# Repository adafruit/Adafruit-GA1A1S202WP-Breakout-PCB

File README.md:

## Adafruit GA1A1S202WP Breakout PCB

<a href="http://www.adafruit.com/products/1384"><br/>
Click here to purchase one from the Adafruit shop</a>

PCB files for the Adafruit GA1A1S202WP Light Sensor. Format is EagleCAD schematic and board layout
* https://www.adafruit.com/products/1384

### DESCRIPTION
Upgrade a project that uses a photocell with the GA1A12S202 analog light sensor. Like a CdS photo-cell, the sensor does not require a microcontroller, the analog voltage output increases with the amount of light shining on the sensor face. This sensor has a lot of improvements that make it better for nearly any project.

The biggest improvement over plain photocells is a true log-lin relationship with light levels. Most light sensors have a linear relationship with light levels, which means that they're not very sensitive to changes in darkened areas and 'max' out very easily when there's a lot of light. Sometimes you can tweak a resistor to make them better in dark or bright light but its hard to get good performance at both ends. This sensor is logarithmic over a large dynamic range of 3 to 55,000 Lux, so it has a lot of sensitivity at low light levels but is also nearly impossible to "max out" so you can use it indoors or outdoors without changing code or calibration. Since the sensor is fabricated on a chip, there are also fewer manufacturing variations, so you won't have to calibrate the sensor from one board to another.

Using the sensor is easy as pie: connect the Vin to 2.3-6VDC, Gnd to ground and measure the analog output on OUT. It will range up to 3V (at extremely bright outdoor sunlight). On an Arduino, just use analogRead() with the OUT pin connected to an analog pin. For more information including graphs, power consumption, etc check out the datasheet in the Tech Details tab. On this breakout we placed a 68KΩ resistor from OUT to ground to turn the current into a voltage.

### License

Adafruit invests time and resources providing this open source design, please support Adafruit and open-source hardware by purchasing products from [Adafruit.com](https://www.adafruit.com)!

Designed by Adafruit Industries. 

Creative Commons Attribution, Share-Alike license, check license.txt for more information All text above must be included in any redistribution - see license.txt for more information.

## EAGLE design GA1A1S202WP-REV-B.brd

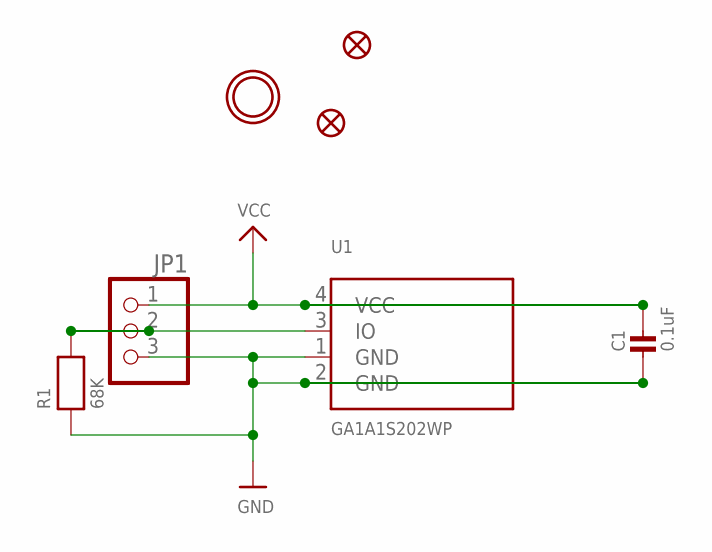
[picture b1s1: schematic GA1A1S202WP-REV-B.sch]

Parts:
C1: 0.1uF; _0805MP
FID1, FID2: FIDUCIAL""; FIDUCIAL_1MM
JP1: HEADER-1X3ROUND; 1X03_ROUND
R1: 68K; _0805MP
U1: GA1A1S202WP
U$3: MOUNTINGHOLE2.5; MOUNTINGHOLE_2.5_PLATED

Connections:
GND: C1.2, JP1.3, R1.1, U1.1 (GND), U1.2 (GND)
unnamed: JP1.2, R1.2, U1.3 (IO)
VCC: C1.1, JP1.1, U1.4 (VCC)

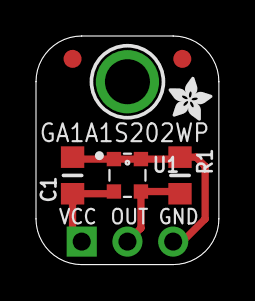
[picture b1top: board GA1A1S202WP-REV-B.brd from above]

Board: 2 copper layers, 10.2 x 12.7 mm, 8 parts (0 on the bottom side), 3 nets.

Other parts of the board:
U$4: ADAFRUIT_2.5MM

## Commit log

2016-09-28 init

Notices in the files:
parts and their libraries:
microbuilder: This work is placed in the public domain, and may be freely used for commercial and non-commercial work with the following conditions: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
